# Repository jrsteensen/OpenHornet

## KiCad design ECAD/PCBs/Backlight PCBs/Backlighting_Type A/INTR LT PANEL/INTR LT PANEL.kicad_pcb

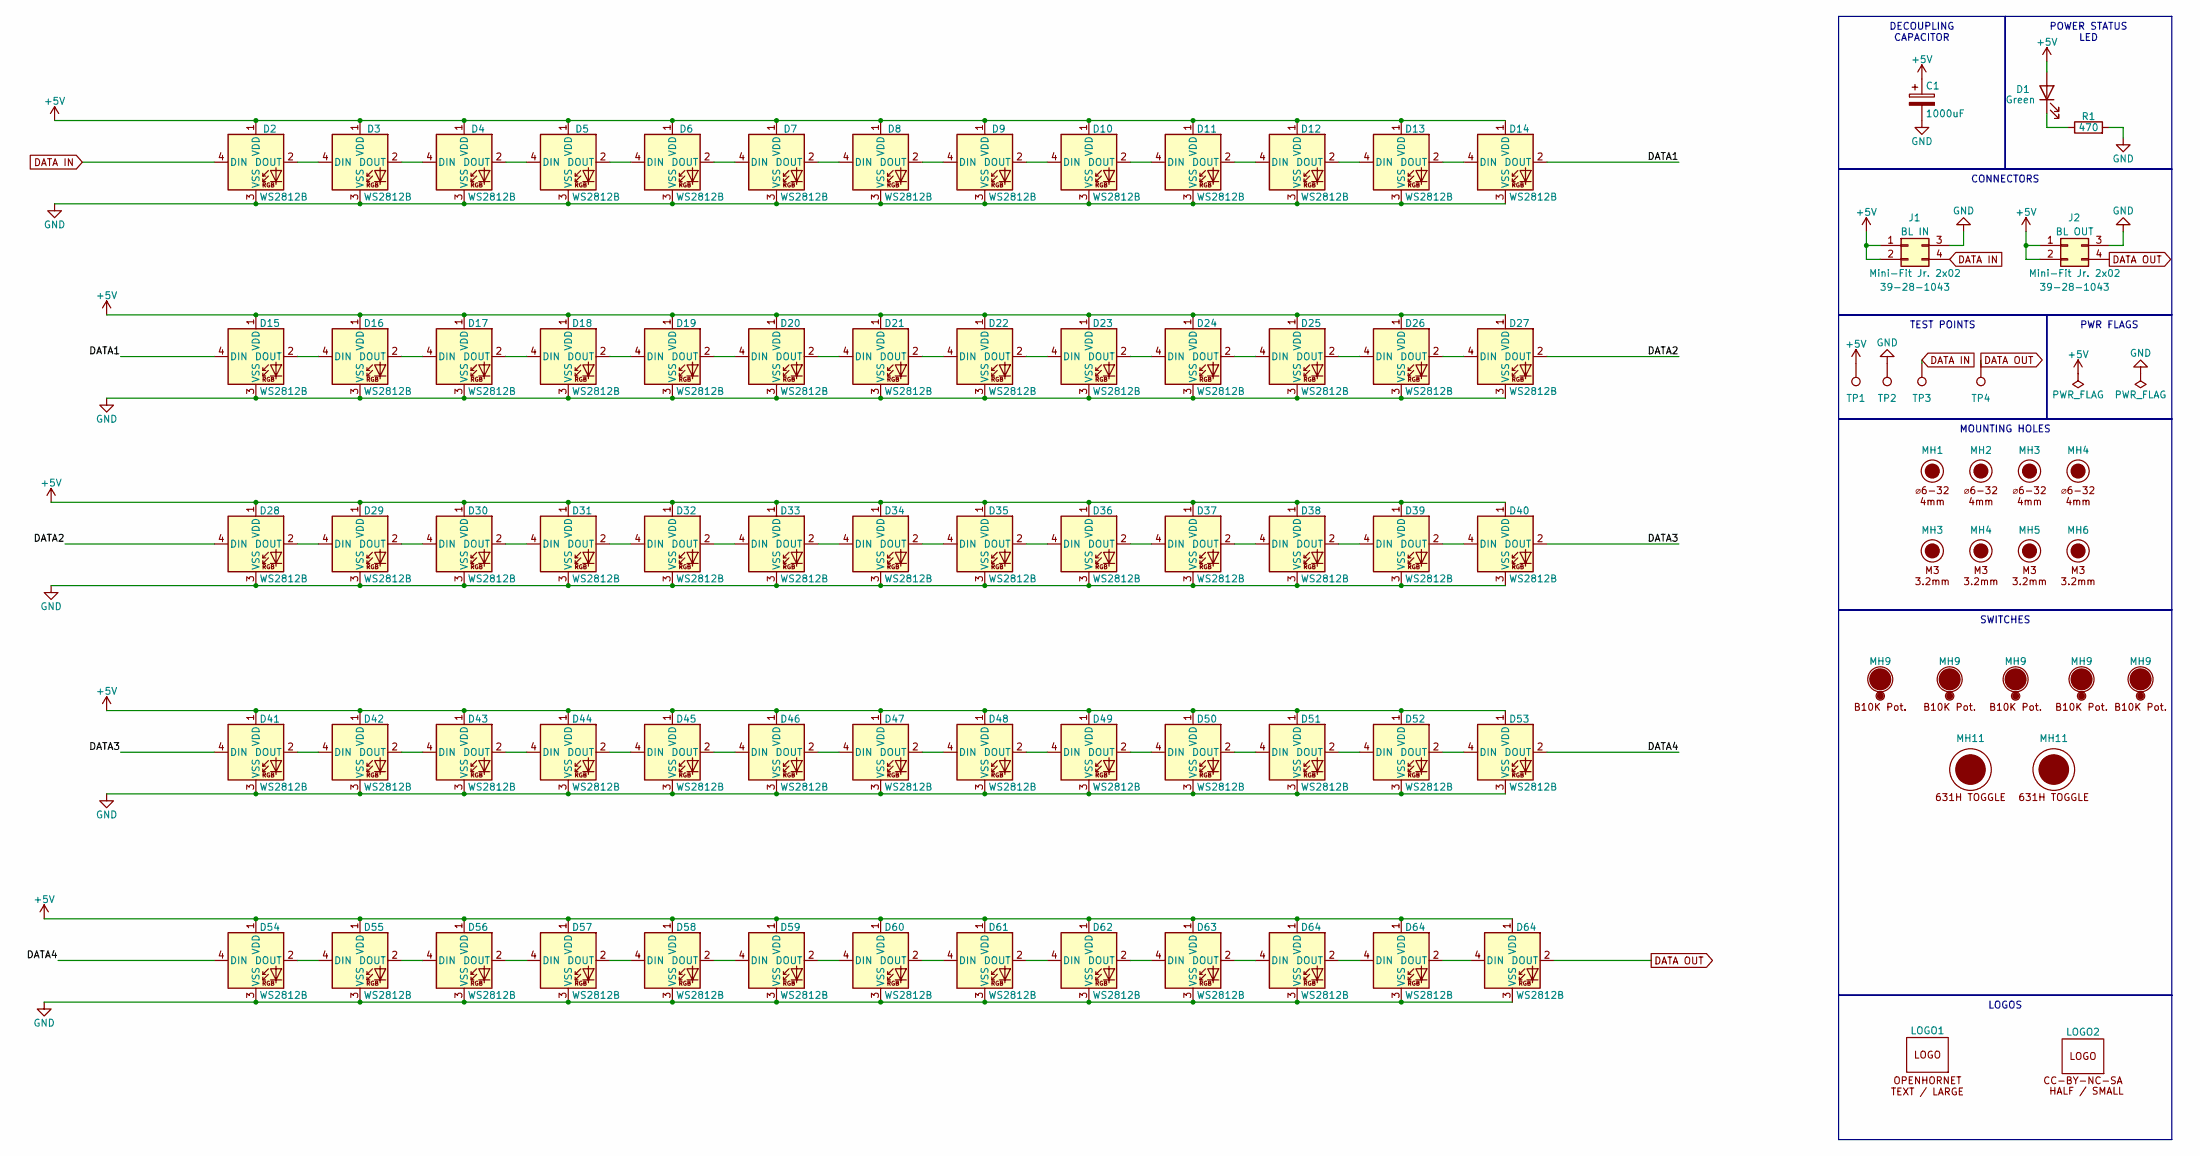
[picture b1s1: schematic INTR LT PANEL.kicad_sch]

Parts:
C1: 1000uF; CP_Elec_8x10; Manufacturer PN UWT0J102MNL1GS; LCSC C445083
D1: Green; LED_D3.0mm; Manufacturer PN 151031VS06000
D2, D3, D4, D5, D6, D7, D8, D9, D10, D11, D12, D13, D14, D15, D16, D17, D18, D19, D20, D21, D22, D23, D24, D25, D26, D27, D28, D29, D30, D31, D32, D33, D34, D35, D36, D37, D38, D39, D40, D41, D42, D43, D44, D45, D46, D47, D48, D49, D50, D51, D52, D53, D54, D55, D56, D57, D58, D59, D60, D61, D62, D63, D64: WS2812B; LED_WS2812B_PLCC4_5.0x5.0mm_P3.2mm; Manufacturer PN WS2812B; LCSC C2761795
J1, J2: Mini-Fit Jr. 2x02; Molex_Mini-Fit_Jr_5566-04A_2x02_P4.20mm_Vertical; Manufacturer PN 39-28-1043; LCSC C293502
LOGO1: LOGO; LOGO_OH_Text_Large
LOGO2: LOGO; LOGO_CC-BY-NC-SA_Half_Small
MH1, MH2: 6x32 / 4mm; MountingHole_6-32_PHS
MH3, MH4, MH5, MH6: M3 / 3.2mm; MountingHole_3.2mm_M3_DIN965
MH9: Pot_B10K; BR10K_Pot_11mm_x_11mm; Manufacturer PN P0915N-FC20BR10K
MH11: Switch_631H; 631HX_Toggle_13mm_x_13mm; Manufacturer PN 631H
R1: 470; R_0603_1608Metric; Manufacturer PN 0603WAF4700T5E; LCSC C23179
TP1, TP2, TP3, TP4: TestPoint; TestPoint_THTPad_D1.5mm_Drill0.7mm

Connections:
+5V: C1.1, D1.2 (A), D2.1 (VDD), D3.1 (VDD), D4.1 (VDD), D5.1 (VDD), D6.1 (VDD), D7.1 (VDD), D8.1 (VDD), D9.1 (VDD), D10.1 (VDD), D11.1 (VDD), D12.1 (VDD), D13.1 (VDD), D14.1 (VDD), D15.1 (VDD), D16.1 (VDD), D17.1 (VDD), D18.1 (VDD), D19.1 (VDD), D20.1 (VDD), D21.1 (VDD), D22.1 (VDD), D23.1 (VDD), D24.1 (VDD), D25.1 (VDD), D26.1 (VDD), D27.1 (VDD), D28.1 (VDD), D29.1 (VDD), D30.1 (VDD), D31.1 (VDD), D32.1 (VDD), D33.1 (VDD), D34.1 (VDD), D35.1 (VDD), D36.1 (VDD), D37.1 (VDD), D38.1 (VDD), D39.1 (VDD), D40.1 (VDD), D41.1 (VDD), D42.1 (VDD), D43.1 (VDD), D44.1 (VDD), D45.1 (VDD), D46.1 (VDD), D47.1 (VDD), D48.1 (VDD), D49.1 (VDD), D50.1 (VDD), D51.1 (VDD), D52.1 (VDD), D53.1 (VDD), D54.1 (VDD), D55.1 (VDD), D56.1 (VDD), D57.1 (VDD), D58.1 (VDD), D59.1 (VDD), D60.1 (VDD), D61.1 (VDD), D62.1 (VDD), D63.1 (VDD), D64.1 (VDD), J1.1, J1.2 (Pin_3), J2.1, J2.2 (Pin_3), TP1.1; also elsewhere on the board
/DATA1: D14.2 (DOUT), D15.4 (DIN)
/DATA2: D27.2 (DOUT), D28.4 (DIN)
/DATA3: D40.2 (DOUT), D41.4 (DIN)
/DATA4: D53.2 (DOUT), D54.4 (DIN)
DATA IN: D2.4 (DIN), J1.4, TP3.1
GND: C1.2, D2.3 (VSS), D3.3 (VSS), D4.3 (VSS), D5.3 (VSS), D6.3 (VSS), D7.3 (VSS), D8.3 (VSS), D9.3 (VSS), D10.3 (VSS), D11.3 (VSS), D12.3 (VSS), D13.3 (VSS), D14.3 (VSS), D15.3 (VSS), D16.3 (VSS), D17.3 (VSS), D18.3 (VSS), D19.3 (VSS), D20.3 (VSS), D21.3 (VSS), D22.3 (VSS), D23.3 (VSS), D24.3 (VSS), D25.3 (VSS), D26.3 (VSS), D27.3 (VSS), D28.3 (VSS), D29.3 (VSS), D30.3 (VSS), D31.3 (VSS), D32.3 (VSS), D33.3 (VSS), D34.3 (VSS), D35.3 (VSS), D36.3 (VSS), D37.3 (VSS), D38.3 (VSS), D39.3 (VSS), D40.3 (VSS), D41.3 (VSS), D42.3 (VSS), D43.3 (VSS), D44.3 (VSS), D45.3 (VSS), D46.3 (VSS), D47.3 (VSS), D48.3 (VSS), D49.3 (VSS), D50.3 (VSS), D51.3 (VSS), D52.3 (VSS), D53.3 (VSS), D54.3 (VSS), D55.3 (VSS), D56.3 (VSS), D57.3 (VSS), D58.3 (VSS), D59.3 (VSS), D60.3 (VSS), D61.3 (VSS), D62.3 (VSS), D63.3 (VSS), D64.3 (VSS), J1.3 (Pin_2), J2.3 (Pin_2), R1.2, TP2.1; also elsewhere on the board
unnamed: D1.1 (K), R1.1
unnamed: D2.2 (DOUT), D3.4 (DIN)
unnamed: D3.2 (DOUT), D4.4 (DIN)
unnamed: D4.2 (DOUT), D5.4 (DIN)
unnamed: D5.2 (DOUT), D6.4 (DIN)
unnamed: D6.2 (DOUT), D7.4 (DIN)
unnamed: D7.2 (DOUT), D8.4 (DIN)
unnamed: D8.2 (DOUT), D9.4 (DIN)
unnamed: D9.2 (DOUT), D10.4 (DIN)
unnamed: D10.2 (DOUT), D11.4 (DIN)
unnamed: D11.2 (DOUT), D12.4 (DIN)
unnamed: D12.2 (DOUT), D13.4 (DIN)
unnamed: D13.2 (DOUT), D14.4 (DIN)
unnamed: D15.2 (DOUT), D16.4 (DIN)
unnamed: D16.2 (DOUT), D17.4 (DIN)
unnamed: D17.2 (DOUT), D18.4 (DIN)
unnamed: D18.2 (DOUT), D19.4 (DIN)
unnamed: D19.2 (DOUT), D20.4 (DIN)
unnamed: D20.2 (DOUT), D21.4 (DIN)
unnamed: D21.2 (DOUT), D22.4 (DIN)
unnamed: D22.2 (DOUT), D23.4 (DIN)
unnamed: D23.2 (DOUT), D24.4 (DIN)
unnamed: D24.2 (DOUT), D25.4 (DIN)
unnamed: D25.2 (DOUT), D26.4 (DIN)
unnamed: D26.2 (DOUT), D27.4 (DIN)
unnamed: D28.2 (DOUT), D29.4 (DIN)
unnamed: D29.2 (DOUT), D30.4 (DIN)
unnamed: D30.2 (DOUT), D31.4 (DIN)
unnamed: D31.2 (DOUT), D32.4 (DIN)
unnamed: D32.2 (DOUT), D33.4 (DIN)
unnamed: D33.2 (DOUT), D34.4 (DIN)
unnamed: D34.2 (DOUT), D35.4 (DIN)
unnamed: D35.2 (DOUT), D36.4 (DIN)
unnamed: D36.2 (DOUT), D37.4 (DIN)
unnamed: D37.2 (DOUT), D38.4 (DIN)
unnamed: D38.2 (DOUT), D39.4 (DIN)
unnamed: D39.2 (DOUT), D40.4 (DIN)
unnamed: D41.2 (DOUT), D42.4 (DIN)
unnamed: D42.2 (DOUT), D43.4 (DIN)
unnamed: D43.2 (DOUT), D44.4 (DIN)
unnamed: D44.2 (DOUT), D45.4 (DIN)
unnamed: D45.2 (DOUT), D46.4 (DIN)
unnamed: D46.2 (DOUT), D47.4 (DIN)
unnamed: D47.2 (DOUT), D48.4 (DIN)
unnamed: D48.2 (DOUT), D49.4 (DIN)
unnamed: D49.2 (DOUT), D50.4 (DIN)
unnamed: D50.2 (DOUT), D51.4 (DIN)
unnamed: D51.2 (DOUT), D52.4 (DIN)
unnamed: D52.2 (DOUT), D53.4 (DIN)
unnamed: D54.2 (DOUT), D55.4 (DIN)
unnamed: D55.2 (DOUT), D56.4 (DIN)
unnamed: D56.2 (DOUT), D57.4 (DIN)
unnamed: D57.2 (DOUT), D58.4 (DIN)
unnamed: D58.2 (DOUT), D59.4 (DIN)
unnamed: D59.2 (DOUT), D60.4 (DIN)
unnamed: D60.2 (DOUT), D61.4 (DIN)
unnamed: D61.2 (DOUT), D62.4 (DIN)
unnamed: D62.2 (DOUT), D63.4 (DIN)

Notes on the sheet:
CONNECTORS
LOGOS
PWR FLAGS
SWITCHES
TEST POINTS
DECOUPLING CAPACITOR
POWER STATUS LED
MOUNTING HOLES

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
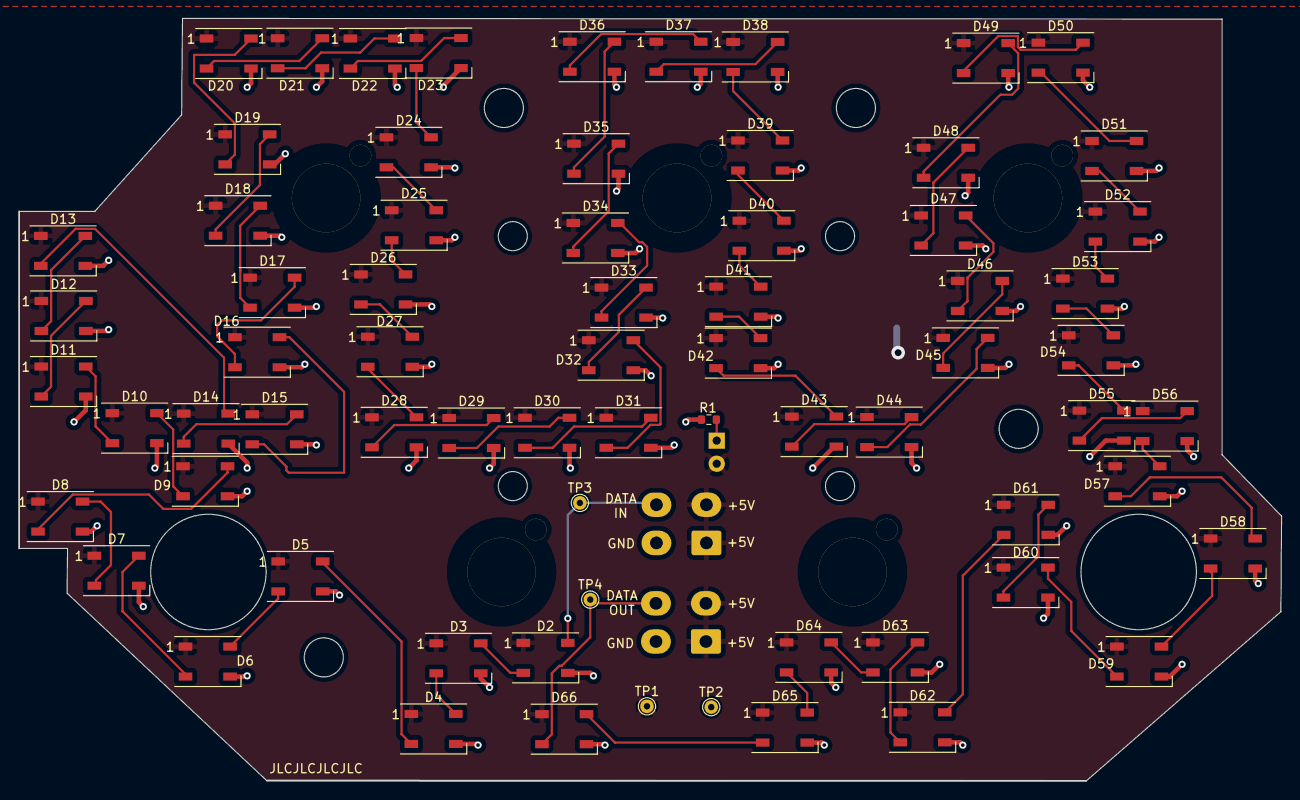
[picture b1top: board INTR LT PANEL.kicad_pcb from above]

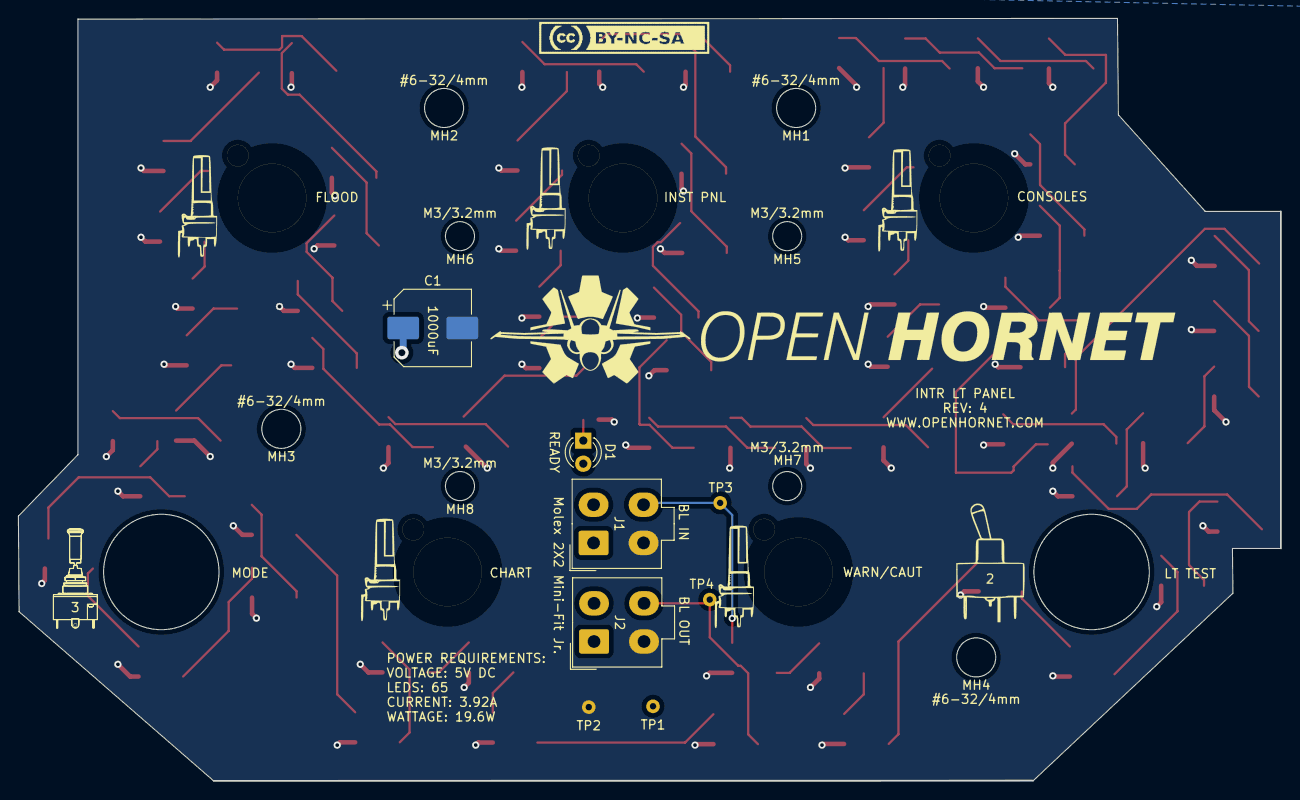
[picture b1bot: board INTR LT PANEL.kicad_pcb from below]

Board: 2 copper layers, 138.9 x 83.9 mm, 98 parts (21 on the bottom side), 69 nets.

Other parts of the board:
D65, D66: WS2812B; LED_WS2812B_PLCC4_5.0x5.0mm_P3.2mm
LOGO3, LOGO4, LOGO5, LOGO7, LOGO8: LOGO; BR10K_Pot_Silkscreen
LOGO6: LOGO; 631H2_Toggle_Silkscreen
LOGO9: LOGO; S3AL_Toggle_Silkscreen
MH7, MH8: M3 / 3.2mm; MountingHole_3.2mm_M3_DIN965
MH10, MH12, MH13: Pot_B10K; BR10K_Pot_11mm_x_11mm
MH14, MH15: Switch_631H; 631HX_Toggle_13mm_x_13mm

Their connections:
+5V: D65.1 (VDD), D66.1 (VDD); also elsewhere on the board
GND: D65.3 (VSS), D66.3 (VSS); also elsewhere on the board
unnamed: D65.2 (DOUT), D66.4 (DIN)

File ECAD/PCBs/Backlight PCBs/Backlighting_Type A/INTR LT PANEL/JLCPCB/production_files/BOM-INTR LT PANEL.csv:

Comment,Designator,Footprint,LCSC
470,R1,R_0603_1608Metric,C23179
WS2812B,"D10,D11,D12,D13,D14,D15,D16,D17,D18,D19,D2,D20,D21,D22,D23,D24,D25,D26,D27,D28,D29,D3,D30,D31,D32,D33,D34,D35,D36,D37,D38,D39,D4,D40,D41,D42,D43,D44,D45,D46,D47,D48,D49,D5,D50,D51,D52,D53,D54,D55,D56,D57,D58,D59,D6,D60,D61,D62,D63,D64,D65,D66,D7,D8,D9",LED_WS2812B_PLCC4_5.0x5.0mm_P3.2mm,C2761795
Mini-Fit Jr. 2x02,"J1,J2",Molex_Mini-Fit_Jr_5566-04A_2x02_P4.20mm_Vertical,C293502
1000uF,C1,CP_Elec_8x10,C445083
Green,D1,LED_D3.0mm,

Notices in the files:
ECAD/PCBs/Backlight PCBs/Backlighting_Type A/INTR LT PANEL/INTR LT PANEL.kicad_pcb:
License: CC BY-NC-SA
parts and their libraries:
https://creativecommons.org/licenses/by-nc-sa/4.0
